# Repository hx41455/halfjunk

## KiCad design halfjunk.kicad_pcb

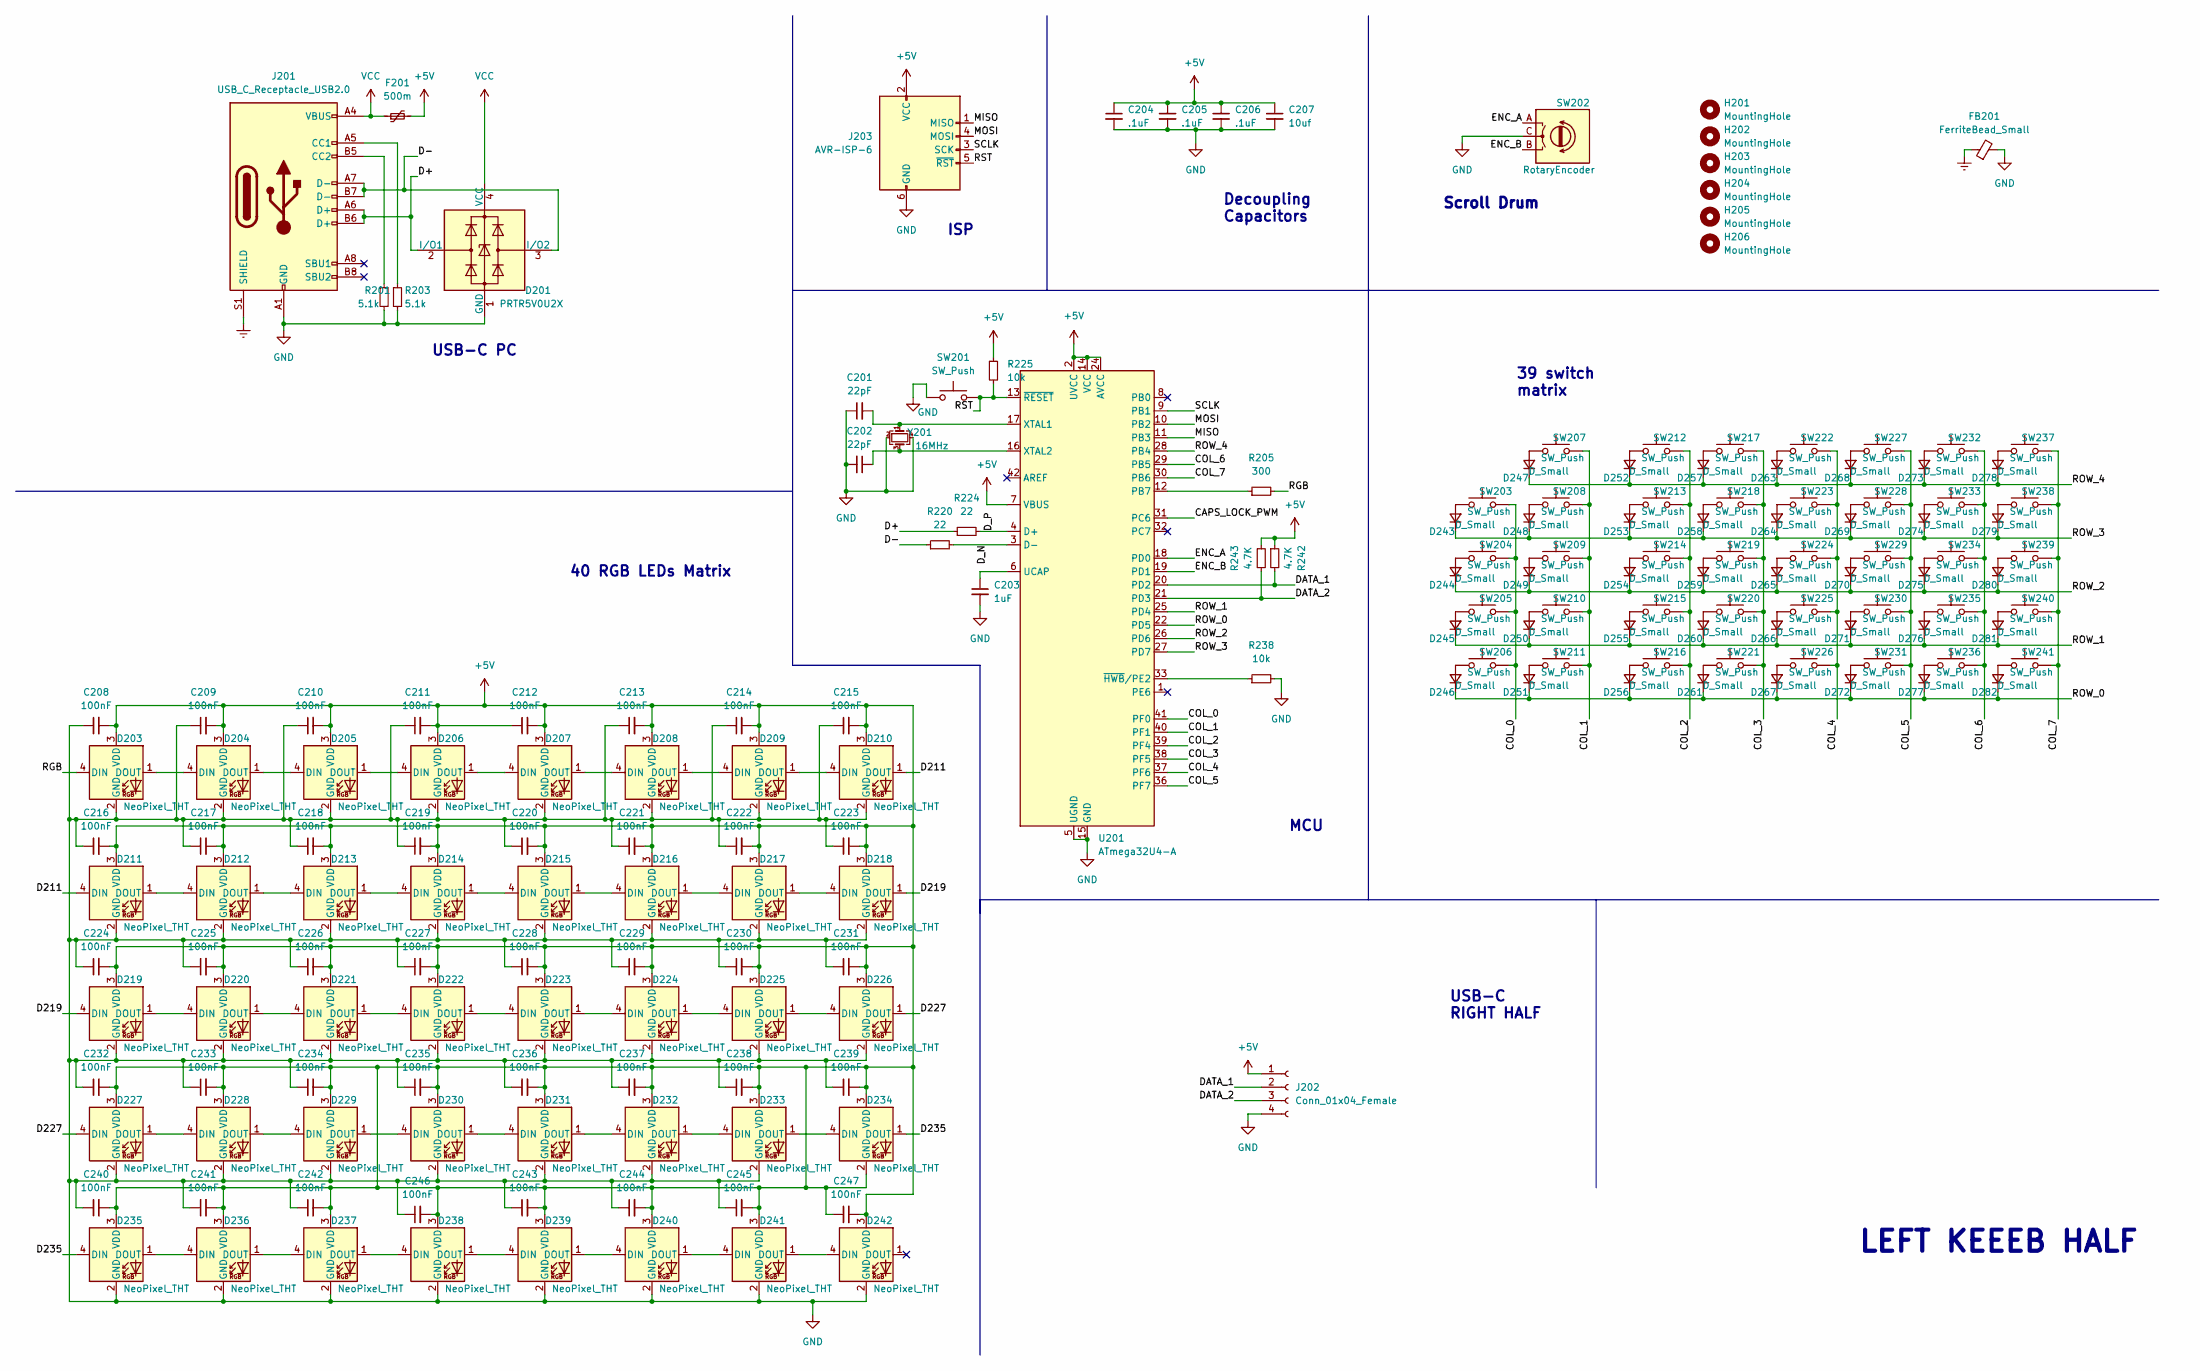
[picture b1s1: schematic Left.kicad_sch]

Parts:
C201, C202: 22pF; C_0402_1005Metric
C203: 1uF; C_0402_1005Metric
C204, C205, C206: .1uF; C_0402_1005Metric
C207: 10uf; C_0402_1005Metric
C208, C209, C210, C211, C212, C213, C214, C215, C216, C217, C218, C219, C220, C221, C222, C223, C224, C225, C226, C227, C228, C229, C230, C231, C232, C233, C234, C235, C236, C237, C238, C239, C240, C241, C242, C243, C244, C245, C246, C247: 100nF; C_0402_1005Metric
D201: PRTR5V0U2X; SOT-143
D203, D204, D205, D206, D207, D208, D209, D210, D211, D212, D213, D214, D215, D216, D217, D218, D219, D220, D221, D222, D223, D224, D225, D226, D227, D228, D229, D230, D231, D232, D233, D234, D235, D236, D237, D238, D239, D240, D241, D242: NeoPixel_THT; LED_RGB_Wuerth-PLCC4_3.2x2.8mm_150141M173100
D243, D244, D245, D246, D247, D248, D249, D250, D251, D252, D253, D254, D255, D256, D257, D258, D259, D260, D261, D263, D264, D265, D266, D267, D268, D269, D270, D271, D272, D273, D274, D275, D276, D277, D278, D279, D280, D281, D282: D_Small; D_SOD-123
F201: 500m; Fuse_0805
FB201: FerriteBead_Small; L_0805_2012Metric_Pad1.15x1.40mm_HandSolder
H201, H202, H203, H204, H205, H206: MountingHole; MountingHole_2.2mm_M2_DIN965_Pad
J201: USB_C_Receptacle_USB2.0; HRO-TYPE-C-31-M-13
J202: Conn_01x04_Female; I2C_Breakout
J203: AVR-ISP-6; ICSP-Header
R201, R203: 5.1k; R_0402_1005Metric
R205: 300; R_0402_1005Metric
R220, R224: 22; R_0402_1005Metric
R225, R238: 10k; R_0402_1005Metric
R242, R243: 4.7K; R_0402_1005Metric
SW201: SW_Push; SW_SPST_TL3342
SW202: RotaryEncoder; kailh_EN97xx_rotary_encoder
SW203, SW204, SW205, SW206, SW207, SW208, SW209, SW210, SW211, SW212, SW217, SW218, SW219, SW220, SW222, SW223, SW224, SW225, SW227, SW228, SW229, SW230, SW232, SW233, SW234, SW235, SW237, SW238, SW239, SW240, SW241: SW_Push; Kailh_socket_PG1350
SW213: SW_Push; Kailh_socket_PG1350_1.5U
SW214: SW_Push; Kailh_socket_PG1350_1.75U
SW215, SW236: SW_Push; Kailh_socket_PG1350_2.25U
SW216, SW221, SW226, SW231: SW_Push; Kailh_socket_PG1350_1.25U
U201: ATmega32U4-A; ATmega32U4
Y201: 16MHz; Crystal_SMD_3225-4Pin_3.2x2.5mm

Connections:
+5V: C204.1, C205.1, C206.1, C207.1, C208.2, C209.2, C210.2, C211.2, C212.1, C212.2, C213.2, C214.2, C215.2, C216.2, C217.2, C218.2, C219.2, C220.2, C221.2, C222.2, C223.2, C224.2, C225.2, C226.2, C227.2, C228.2, C229.2, C230.2, C231.2, C232.2, C233.2, C234.2, C235.2, C236.2, C237.2, C238.2, C239.2, C240.2, C241.2, C242.2, C243.2, C244.2, C245.2, C246.2, C247.1, C247.2, D203.3 (VDD), D204.3 (VDD), D205.3 (VDD), D206.3 (VDD), D207.3 (VDD), D208.3 (VDD), D209.3 (VDD), D210.3 (VDD), D211.3 (VDD), D212.3 (VDD), D213.3 (VDD), D214.3 (VDD), D215.3 (VDD), D216.3 (VDD), D217.3 (VDD), D218.3 (VDD), D219.3 (VDD), D220.3 (VDD), D221.3 (VDD), D222.3 (VDD), D223.3 (VDD), D224.3 (VDD), D225.3 (VDD), D226.3 (VDD), D227.3 (VDD), D228.3 (VDD), D229.3 (VDD), D230.3 (VDD), D231.3 (VDD), D232.3 (VDD), D233.3 (VDD), D234.2 (GND), D234.3 (VDD), D235.3 (VDD), D236.3 (VDD), D237.3 (VDD), D238.3 (VDD), D239.3 (VDD), D240.3 (VDD), D241.3 (VDD), D242.3 (VDD), F201.2, J202.1, J203.2 (VCC), R225.1, R242.1, R243.1, U201.2 (UVCC), U201.7 (VBUS), U201.14 (VCC), U201.24 (AVCC), U201.34 (VCC), U201.44 (AVCC); also elsewhere on the board
/Left/CAPS_LOCK_PWM: U201.31 (PC6)
/Left/COL_0: SW203.2, SW204.2, SW205.2, SW206.2, U201.41 (PF0)
/Left/COL_1: SW207.2, SW208.2, SW209.2, SW210.2, SW211.2, U201.40 (PF1)
/Left/COL_2: SW212.2, SW213.2, SW214.2, SW215.2, SW216.2, U201.39 (PF4)
/Left/COL_3: SW217.2, SW218.2, SW219.2, SW220.2, SW221.2, U201.38 (PF5)
/Left/COL_4: SW222.2, SW223.2, SW224.2, SW225.2, SW226.2, U201.37 (PF6)
/Left/COL_5: SW227.2, SW228.2, SW229.2, SW230.2, SW231.2, U201.36 (PF7)
/Left/COL_6: SW232.2, SW233.2, SW234.2, SW235.2, SW236.2, U201.29 (PB5)
/Left/COL_7: SW237.2, SW238.2, SW239.2, SW240.2, SW241.2, U201.30 (PB6)
/Left/D211: D210.1 (DOUT), D211.4 (DIN)
/Left/D219: D218.1 (DOUT), D219.4 (DIN)
/Left/D227: D226.1 (DOUT), D227.4 (DIN)
/Left/D235: D234.1 (DOUT), D235.4 (DIN)
/Left/D+: D201.2 (I/O1), J201.A6 (D+), J201.B6 (D+), R224.1
/Left/D-: D201.3 (I/O2), J201.A7 (D-), J201.B7 (D-), R220.1
/Left/DATA_1: J202.2, R242.2, U201.20 (PD2)
/Left/DATA_2: J202.3, R243.2, U201.21 (PD3)
/Left/D_N: R220.2, U201.3 (D-)
/Left/D_P: R224.2, U201.4 (D+)
/Left/ENC_A: SW202.A, U201.18 (PD0)
/Left/ENC_B: SW202.B, U201.19 (PD1)
/Left/MISO: J203.1 (MISO), U201.11 (PB3)
/Left/MOSI: J203.4 (MOSI), U201.10 (PB2)
/Left/RGB: D203.4 (DIN), R205.2
/Left/ROW_0: D246.1 (K), D251.1 (K), D256.1 (K), D261.1 (K), D267.1 (K), D272.1 (K), D277.1 (K), D282.1 (K), U201.22 (PD5)
/Left/ROW_1: D245.1 (K), D250.1 (K), D255.1 (K), D260.1 (K), D266.1 (K), D271.1 (K), D276.1 (K), D281.1 (K), U201.25 (PD4)
/Left/ROW_2: D244.1 (K), D249.1 (K), D254.1 (K), D259.1 (K), D265.1 (K), D270.1 (K), D275.1 (K), D280.1 (K), U201.26 (PD6)
/Left/ROW_3: D243.1 (K), D248.1 (K), D253.1 (K), D258.1 (K), D264.1 (K), D269.1 (K), D274.1 (K), D279.1 (K), U201.27 (PD7)
/Left/ROW_4: D247.1 (K), D252.1 (K), D257.1 (K), D263.1 (K), D268.1 (K), D273.1 (K), D278.1 (K), U201.28 (PB4)
/Left/RST: J203.5 (~RST), R225.2, SW201.2, U201.13 (~RESET)
/Left/SCLK: J203.3 (SCK), U201.9 (PB1)
Earth: FB201.1, J201.S1 (SHIELD); also elsewhere on the board
GND: C201.1, C202.2, C203.2, C204.2, C205.2, C206.2, C207.2, C208.1, C209.1, C210.1, C211.1, C213.1, C214.1, C215.1, C216.1, C217.1, C218.1, C219.1, C220.1, C221.1, C222.1, C223.1, C224.1, C225.1, C226.1, C227.1, C228.1, C229.1, C230.1, C231.1, C232.1, C233.1, C234.1, C235.1, C236.1, C237.1, C238.1, C239.1, C240.1, C241.1, C242.1, C243.1, C244.1, C245.1, C246.1, D201.1 (GND), D203.2 (GND), D204.2 (GND), D205.2 (GND), D206.2 (GND), D207.2 (GND), D208.2 (GND), D209.2 (GND), D210.2 (GND), D211.2 (GND), D212.2 (GND), D213.2 (GND), D214.2 (GND), D215.2 (GND), D216.2 (GND), D217.2 (GND), D218.2 (GND), D219.2 (GND), D220.2 (GND), D221.2 (GND), D222.2 (GND), D223.2 (GND), D224.2 (GND), D225.2 (GND), D226.2 (GND), D227.2 (GND), D228.2 (GND), D229.2 (GND), D230.2 (GND), D231.2 (GND), D232.2 (GND), D233.2 (GND), D235.2 (GND), D236.2 (GND), D237.2 (GND), D238.2 (GND), D239.2 (GND), D240.2 (GND), D241.2 (GND), D242.2 (GND), FB201.2, J201.A1 (GND), J201.A12 (GND), J201.B1 (GND), J201.B12 (GND), J202.4, J203.6 (GND), R201.2, R203.2, R238.2, SW201.1, SW202.C, U201.5 (UGND), U201.15 (GND), U201.23 (GND), U201.35 (GND), U201.43 (GND), Y201.2, Y201.4; also elsewhere on the board
unnamed: C201.2, U201.17 (XTAL1), Y201.1
unnamed: C202.1, U201.16 (XTAL2), Y201.3
unnamed: C203.1, U201.6 (UCAP)
unnamed: D203.1 (DOUT), D204.4 (DIN)
unnamed: D204.1 (DOUT), D205.4 (DIN)
unnamed: D205.1 (DOUT), D206.4 (DIN)
unnamed: D206.1 (DOUT), D207.4 (DIN)
unnamed: D207.1 (DOUT), D208.4 (DIN)
unnamed: D208.1 (DOUT), D209.4 (DIN)
unnamed: D209.1 (DOUT), D210.4 (DIN)
unnamed: D211.1 (DOUT), D212.4 (DIN)
unnamed: D212.1 (DOUT), D213.4 (DIN)
unnamed: D213.1 (DOUT), D214.4 (DIN)
unnamed: D214.1 (DOUT), D215.4 (DIN)
unnamed: D215.1 (DOUT), D216.4 (DIN)
unnamed: D216.1 (DOUT), D217.4 (DIN)
unnamed: D217.1 (DOUT), D218.4 (DIN)
unnamed: D219.1 (DOUT), D220.4 (DIN)
unnamed: D220.1 (DOUT), D221.4 (DIN)
unnamed: D221.1 (DOUT), D222.4 (DIN)
unnamed: D222.1 (DOUT), D223.4 (DIN)
unnamed: D223.1 (DOUT), D224.4 (DIN)
unnamed: D224.1 (DOUT), D225.4 (DIN)
unnamed: D225.1 (DOUT), D226.4 (DIN)
unnamed: D227.1 (DOUT), D228.4 (DIN)
unnamed: D228.1 (DOUT), D229.4 (DIN)
unnamed: D229.1 (DOUT), D230.4 (DIN)
unnamed: D230.1 (DOUT), D231.4 (DIN)
unnamed: D231.1 (DOUT), D232.4 (DIN)
unnamed: D232.1 (DOUT), D233.4 (DIN)
unnamed: D233.1 (DOUT), D234.4 (DIN)
unnamed: D235.1 (DOUT), D236.4 (DIN)
unnamed: D236.1 (DOUT), D237.4 (DIN)
unnamed: D237.1 (DOUT), D238.4 (DIN)
unnamed: D238.1 (DOUT), D239.4 (DIN)
unnamed: D239.1 (DOUT), D240.4 (DIN)
unnamed: D240.1 (DOUT), D241.4 (DIN)
unnamed: D241.1 (DOUT), D242.4 (DIN)
unnamed: D243.2 (A), SW203.1
unnamed: D244.2 (A), SW204.1
unnamed: D245.2 (A), SW205.1
unnamed: D246.2 (A), SW206.1
unnamed: D247.2 (A), SW207.1
unnamed: D248.2 (A), SW208.1
unnamed: D249.2 (A), SW209.1
unnamed: D250.2 (A), SW210.1
unnamed: D251.2 (A), SW211.1
unnamed: D252.2 (A), SW212.1
unnamed: D253.2 (A), SW213.1
unnamed: D254.2 (A), SW214.1
unnamed: D255.2 (A), SW215.1
unnamed: D256.2 (A), SW216.1
unnamed: D257.2 (A), SW217.1
unnamed: D258.2 (A), SW218.1
unnamed: D259.2 (A), SW219.1
unnamed: D260.2 (A), SW220.1
unnamed: D261.2 (A), SW221.1
unnamed: D263.2 (A), SW222.1
unnamed: D264.2 (A), SW223.1
unnamed: D265.2 (A), SW224.1
unnamed: D266.2 (A), SW225.1
unnamed: D267.2 (A), SW226.1
unnamed: D268.2 (A), SW227.1
unnamed: D269.2 (A), SW228.1
unnamed: D270.2 (A), SW229.1
unnamed: D271.2 (A), SW230.1
unnamed: D272.2 (A), SW231.1
unnamed: D273.2 (A), SW232.1
unnamed: D274.2 (A), SW233.1
unnamed: D275.2 (A), SW234.1
unnamed: D276.2 (A), SW235.1
unnamed: D277.2 (A), SW236.1
unnamed: D278.2 (A), SW237.1
unnamed: D279.2 (A), SW238.1
unnamed: D280.2 (A), SW239.1
unnamed: D281.2 (A), SW240.1
unnamed: D282.2 (A), SW241.1
unnamed: J201.A5 (CC1), R203.1
unnamed: J201.B5 (CC2), R201.1
unnamed: R205.1, U201.12 (PB7)
unnamed: R238.1, U201.33 (~HWB/PE2)
VCC: D201.4 (VCC), F201.1, J201.A4 (VBUS), J201.A9 (VBUS), J201.B4 (VBUS), J201.B9 (VBUS); also elsewhere on the board

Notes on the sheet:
39 switch matrix
USB-C RIGHT HALF
ISP
USB-C PC
40 RGB LEDs Matrix
Decoupling Capacitors
MCU
LEFT KEEEB HALF
Scroll Drum

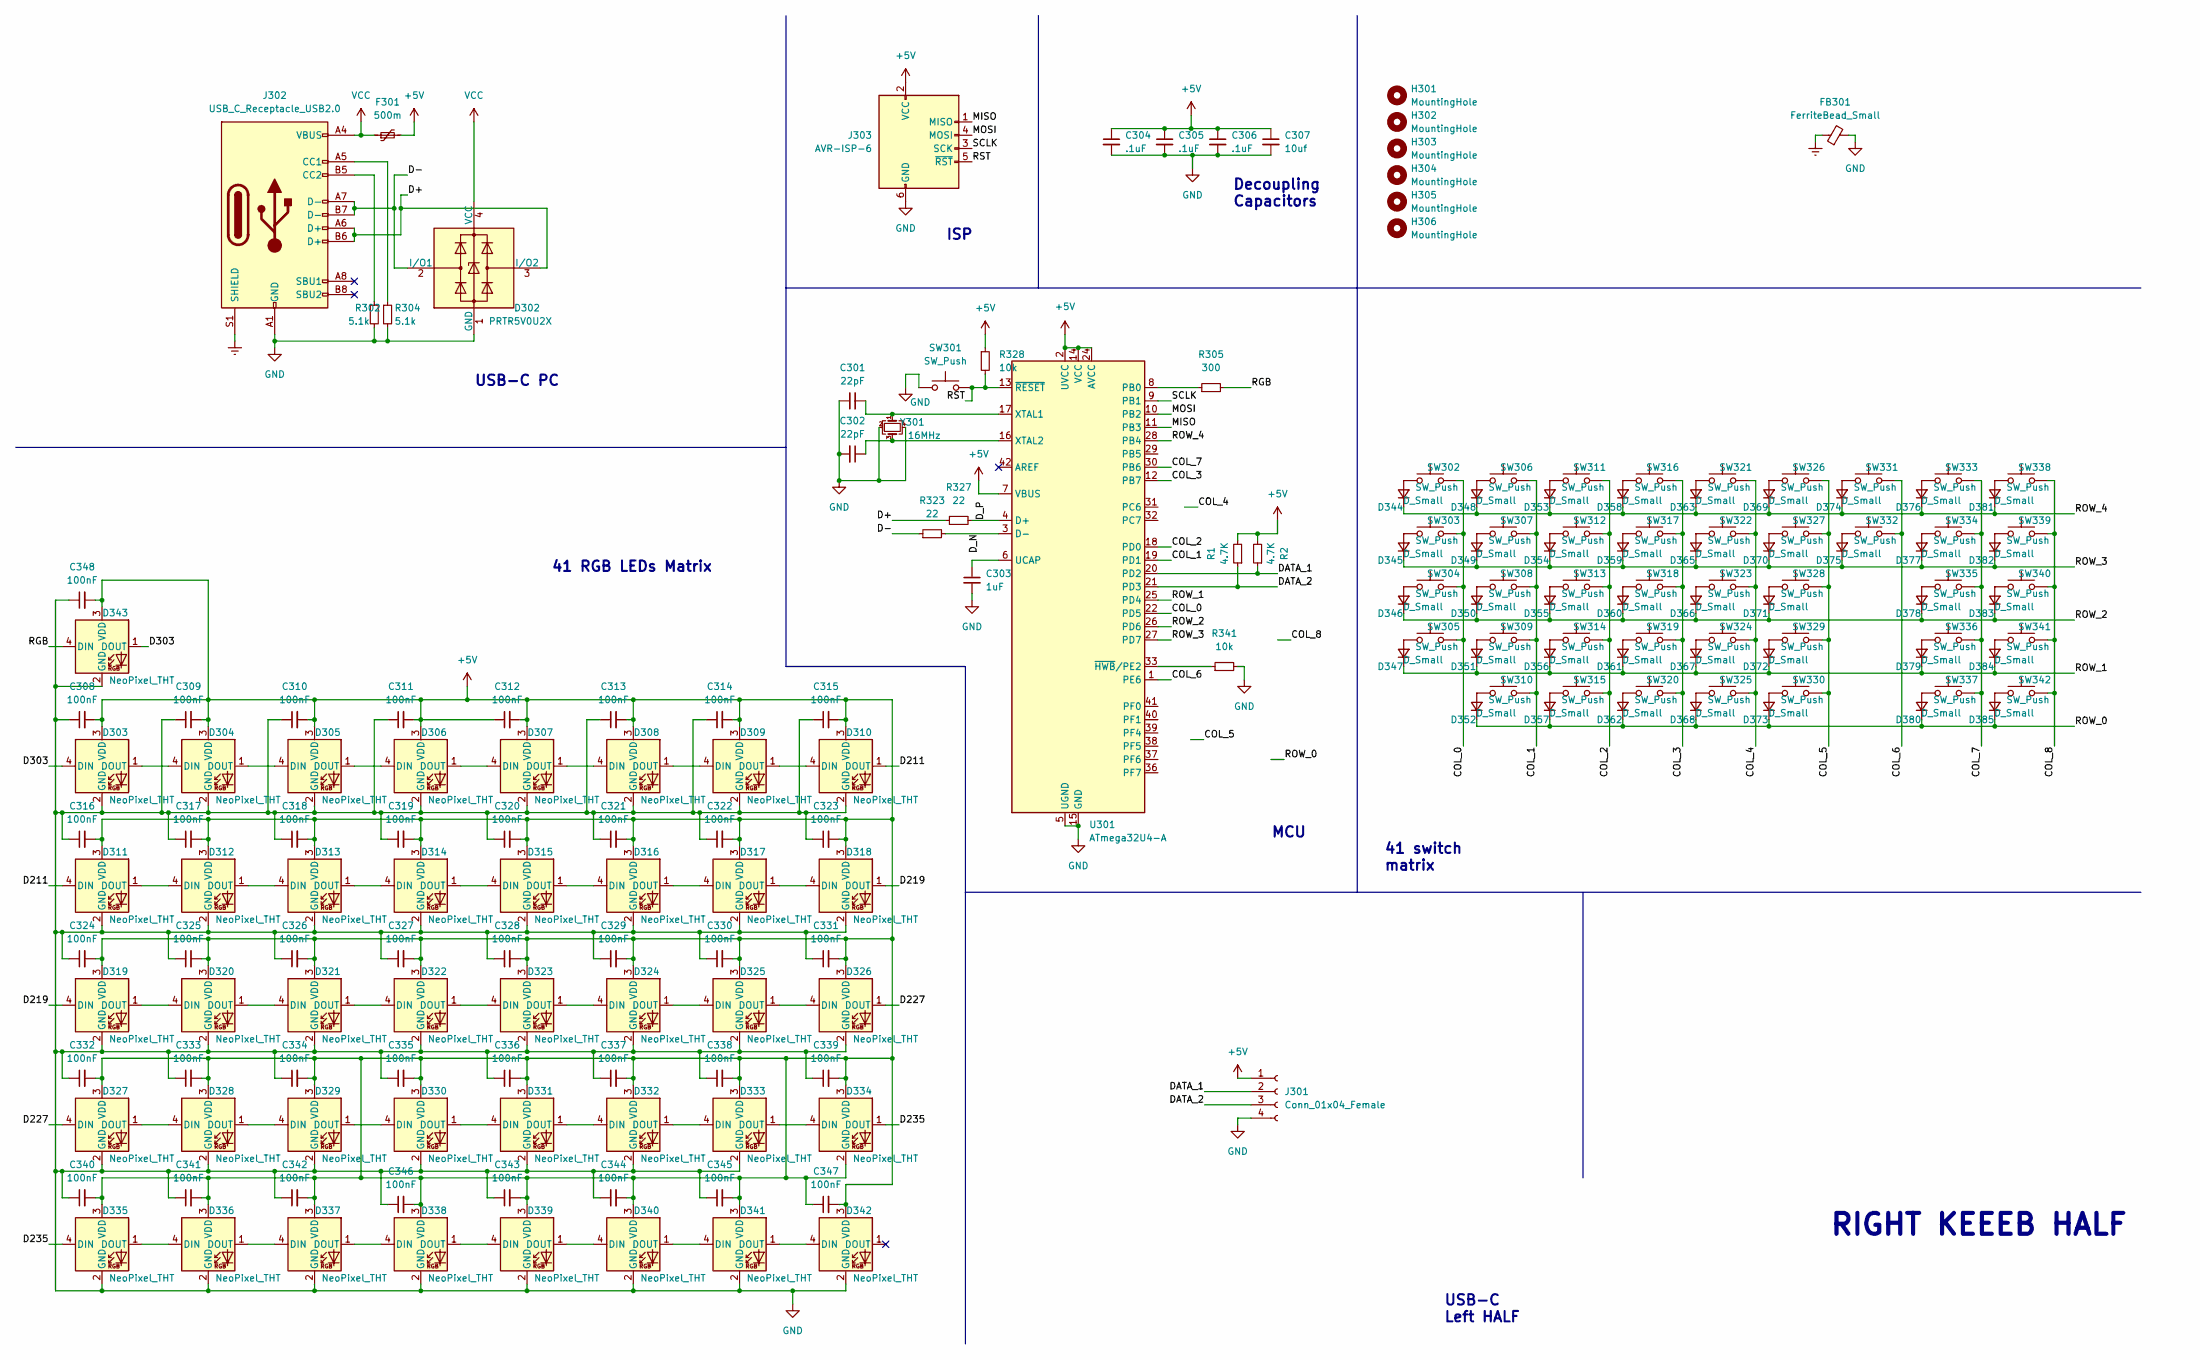
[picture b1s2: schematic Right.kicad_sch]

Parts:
C301, C302: 22pF; C_0402_1005Metric
C303: 1uF; C_0402_1005Metric
C304, C305, C306: .1uF; C_0402_1005Metric
C307: 10uf; C_0402_1005Metric
C308, C309, C310, C311, C312, C313, C314, C315, C316, C317, C318, C319, C320, C321, C322, C323, C324, C325, C326, C327, C328, C329, C330, C331, C332, C333, C334, C335, C336, C337, C338, C339, C340, C341, C342, C343, C344, C345, C346, C347, C348: 100nF; C_0402_1005Metric
D302: PRTR5V0U2X; SOT-143
D303, D304, D305, D306, D307, D308, D309, D310, D311, D312, D313, D314, D315, D316, D317, D318, D319, D320, D321, D322, D323, D324, D325, D326, D327, D328, D329, D330, D331, D332, D333, D334, D335, D336, D337, D338, D339, D340, D341, D342, D343: NeoPixel_THT; LED_RGB_Wuerth-PLCC4_3.2x2.8mm_150141M173100
D344, D345, D346, D347, D348, D349, D350, D351, D352, D353, D354, D355, D356, D357, D358, D359, D360, D361, D362, D363, D365, D366, D367, D368, D369, D370, D371, D372, D373, D374, D375, D376, D377, D378, D379, D380, D381, D382, D383, D384, D385: D_Small; D_SOD-123
F301: 500m; Fuse_0805
FB301: FerriteBead_Small; L_0805_2012Metric_Pad1.15x1.40mm_HandSolder
H301, H302, H303, H304, H305, H306: MountingHole; MountingHole_2.2mm_M2_DIN965_Pad
J301: Conn_01x04_Female; I2C_Breakout
J302: USB_C_Receptacle_USB2.0; HRO-TYPE-C-31-M-13
J303: AVR-ISP-6; ICSP-Header
R1, R2: 4.7K; R_0402_1005Metric
R302, R304: 5.1k; R_0402_1005Metric
R305: 300; R_0402_1005Metric
R323, R327: 22; R_0402_1005Metric
R328, R341: 10k; R_0402_1005Metric
SW301: SW_Push; SW_SPST_TL3342
SW302, SW303, SW304, SW305, SW306, SW307, SW308, SW309, SW311, SW312, SW313, SW314, SW316, SW317, SW318, SW319, SW320, SW321, SW322, SW323, SW324, SW325, SW326, SW327, SW328, SW330, SW331, SW332, SW333, SW336, SW337, SW338, SW339, SW340, SW341, SW342: SW_Push; Kailh_socket_PG1350
SW310, SW335: SW_Push; Kailh_socket_PG1350_2.25U
SW315: SW_Push; Kailh_socket_PG1350_1.25U
SW329: SW_Push; Kailh_socket_PG1350_1.75U
SW334: SW_Push; Kailh_socket_PG1350_1.5U
U301: ATmega32U4-A; ATmega32U4
Y301: 16MHz; Crystal_SMD_3225-4Pin_3.2x2.5mm

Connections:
+5V: C304.1, C305.1, C306.1, C307.1, C308.2, C309.2, C310.2, C311.2, C312.1, C312.2, C313.2, C314.2, C315.2, C316.2, C317.2, C318.2, C319.2, C320.2, C321.2, C322.2, C323.2, C324.2, C325.2, C326.2, C327.2, C328.2, C329.2, C330.2, C331.2, C332.2, C333.2, C334.2, C335.2, C336.2, C337.2, C338.2, C339.2, C340.2, C341.2, C342.2, C343.2, C344.2, C345.2, C346.2, C347.1, C347.2, C348.2, D303.3 (VDD), D304.3 (VDD), D305.3 (VDD), D306.3 (VDD), D307.3 (VDD), D308.3 (VDD), D309.3 (VDD), D310.3 (VDD), D311.3 (VDD), D312.3 (VDD), D313.3 (VDD), D314.3 (VDD), D315.3 (VDD), D316.3 (VDD), D317.3 (VDD), D318.3 (VDD), D319.3 (VDD), D320.3 (VDD), D321.3 (VDD), D322.3 (VDD), D323.3 (VDD), D324.3 (VDD), D325.3 (VDD), D326.3 (VDD), D327.3 (VDD), D328.3 (VDD), D329.3 (VDD), D330.3 (VDD), D331.3 (VDD), D332.3 (VDD), D333.3 (VDD), D334.2 (GND), D334.3 (VDD), D335.3 (VDD), D336.3 (VDD), D337.3 (VDD), D338.3 (VDD), D339.3 (VDD), D340.3 (VDD), D341.3 (VDD), D342.3 (VDD), D343.3 (VDD), F301.2, J301.1, J303.2 (VCC), R1.2, R2.2, R328.1, U301.2 (UVCC), U301.7 (VBUS), U301.14 (VCC), U301.24 (AVCC), U301.34 (VCC), U301.44 (AVCC); also elsewhere on the board
/Right/COL_0: SW302.2, SW303.2, SW304.2, SW305.2, U301.22 (PD5)
/Right/COL_1: SW306.2, SW307.2, SW308.2, SW309.2, SW310.2, U301.19 (PD1)
/Right/COL_2: SW311.2, SW312.2, SW313.2, SW314.2, SW315.2, U301.18 (PD0)
/Right/COL_3: SW316.2, SW317.2, SW318.2, SW319.2, SW320.2, U301.12 (PB7)
/Right/COL_4: SW321.2, SW322.2, SW323.2, SW324.2, SW325.2
/Right/COL_5: SW326.2, SW327.2, SW328.2, SW329.2, SW330.2
/Right/COL_6: SW331.2, SW332.2, U301.1 (PE6)
/Right/COL_7: SW333.2, SW334.2, SW335.2, SW336.2, SW337.2, U301.30 (PB6)
/Right/COL_8: SW338.2, SW339.2, SW340.2, SW341.2, SW342.2
/Right/D211: D310.1 (DOUT), D311.4 (DIN)
/Right/D219: D318.1 (DOUT), D319.4 (DIN)
/Right/D227: D326.1 (DOUT), D327.4 (DIN)
/Right/D235: D334.1 (DOUT), D335.4 (DIN)
/Right/D303: D303.4 (DIN), D343.1 (DOUT)
/Right/D+: D302.3 (I/O2), J302.A6 (D+), J302.B6 (D+), R327.1
/Right/D-: D302.2 (I/O1), J302.A7 (D-), J302.B7 (D-), R323.1
/Right/DATA_1: J301.2, R2.1, U301.20 (PD2)
/Right/DATA_2: J301.3, R1.1, U301.21 (PD3)
/Right/D_N: R323.2, U301.3 (D-)
/Right/D_P: R327.2, U301.4 (D+)
/Right/MISO: J303.1 (MISO), U301.11 (PB3)
/Right/MOSI: J303.4 (MOSI), U301.10 (PB2)
/Right/RGB: D343.4 (DIN), R305.2
/Right/ROW_0: D352.1 (K), D357.1 (K), D362.1 (K), D368.1 (K), D373.1 (K), D380.1 (K), D385.1 (K)
/Right/ROW_1: D347.1 (K), D351.1 (K), D356.1 (K), D361.1 (K), D367.1 (K), D372.1 (K), D379.1 (K), D384.1 (K), U301.25 (PD4)
/Right/ROW_2: D346.1 (K), D350.1 (K), D355.1 (K), D360.1 (K), D366.1 (K), D371.1 (K), D378.1 (K), D383.1 (K), U301.26 (PD6)
/Right/ROW_3: D345.1 (K), D349.1 (K), D354.1 (K), D359.1 (K), D365.1 (K), D370.1 (K), D375.1 (K), D377.1 (K), D382.1 (K), U301.27 (PD7)
/Right/ROW_4: D344.1 (K), D348.1 (K), D353.1 (K), D358.1 (K), D363.1 (K), D369.1 (K), D374.1 (K), D376.1 (K), D381.1 (K), U301.28 (PB4)
/Right/RST: J303.5 (~RST), R328.2, SW301.2, U301.13 (~RESET)
/Right/SCLK: J303.3 (SCK), U301.9 (PB1)
Earth: FB301.1, J302.S1 (SHIELD); also elsewhere on the board
GND: C301.1, C302.2, C303.2, C304.2, C305.2, C306.2, C307.2, C308.1, C309.1, C310.1, C311.1, C313.1, C314.1, C315.1, C316.1, C317.1, C318.1, C319.1, C320.1, C321.1, C322.1, C323.1, C324.1, C325.1, C326.1, C327.1, C328.1, C329.1, C330.1, C331.1, C332.1, C333.1, C334.1, C335.1, C336.1, C337.1, C338.1, C339.1, C340.1, C341.1, C342.1, C343.1, C344.1, C345.1, C346.1, C348.1, D302.1 (GND), D303.2 (GND), D304.2 (GND), D305.2 (GND), D306.2 (GND), D307.2 (GND), D308.2 (GND), D309.2 (GND), D310.2 (GND), D311.2 (GND), D312.2 (GND), D313.2 (GND), D314.2 (GND), D315.2 (GND), D316.2 (GND), D317.2 (GND), D318.2 (GND), D319.2 (GND), D320.2 (GND), D321.2 (GND), D322.2 (GND), D323.2 (GND), D324.2 (GND), D325.2 (GND), D326.2 (GND), D327.2 (GND), D328.2 (GND), D329.2 (GND), D330.2 (GND), D331.2 (GND), D332.2 (GND), D333.2 (GND), D335.2 (GND), D336.2 (GND), D337.2 (GND), D338.2 (GND), D339.2 (GND), D340.2 (GND), D341.2 (GND), D342.2 (GND), D343.2 (GND), FB301.2, J301.4, J302.A1 (GND), J302.A12 (GND), J302.B1 (GND), J302.B12 (GND), J303.6 (GND), R302.2, R304.2, R341.2, SW301.1, U301.5 (UGND), U301.15 (GND), U301.23 (GND), U301.35 (GND), U301.43 (GND), Y301.2, Y301.4; also elsewhere on the board
unnamed: C301.2, U301.17 (XTAL1), Y301.1
unnamed: C302.1, U301.16 (XTAL2), Y301.3
unnamed: C303.1, U301.6 (UCAP)
unnamed: D303.1 (DOUT), D304.4 (DIN)
unnamed: D304.1 (DOUT), D305.4 (DIN)
unnamed: D305.1 (DOUT), D306.4 (DIN)
unnamed: D306.1 (DOUT), D307.4 (DIN)
unnamed: D307.1 (DOUT), D308.4 (DIN)
unnamed: D308.1 (DOUT), D309.4 (DIN)
unnamed: D309.1 (DOUT), D310.4 (DIN)
unnamed: D311.1 (DOUT), D312.4 (DIN)
unnamed: D312.1 (DOUT), D313.4 (DIN)
unnamed: D313.1 (DOUT), D314.4 (DIN)
unnamed: D314.1 (DOUT), D315.4 (DIN)
unnamed: D315.1 (DOUT), D316.4 (DIN)
unnamed: D316.1 (DOUT), D317.4 (DIN)
unnamed: D317.1 (DOUT), D318.4 (DIN)
unnamed: D319.1 (DOUT), D320.4 (DIN)
unnamed: D320.1 (DOUT), D321.4 (DIN)
unnamed: D321.1 (DOUT), D322.4 (DIN)
unnamed: D322.1 (DOUT), D323.4 (DIN)
unnamed: D323.1 (DOUT), D324.4 (DIN)
unnamed: D324.1 (DOUT), D325.4 (DIN)
unnamed: D325.1 (DOUT), D326.4 (DIN)
unnamed: D327.1 (DOUT), D328.4 (DIN)
unnamed: D328.1 (DOUT), D329.4 (DIN)
unnamed: D329.1 (DOUT), D330.4 (DIN)
unnamed: D330.1 (DOUT), D331.4 (DIN)
unnamed: D331.1 (DOUT), D332.4 (DIN)
unnamed: D332.1 (DOUT), D333.4 (DIN)
unnamed: D333.1 (DOUT), D334.4 (DIN)
unnamed: D335.1 (DOUT), D336.4 (DIN)
unnamed: D336.1 (DOUT), D337.4 (DIN)
unnamed: D337.1 (DOUT), D338.4 (DIN)
unnamed: D338.1 (DOUT), D339.4 (DIN)
unnamed: D339.1 (DOUT), D340.4 (DIN)
unnamed: D340.1 (DOUT), D341.4 (DIN)
unnamed: D341.1 (DOUT), D342.4 (DIN)
unnamed: D344.2 (A), SW302.1
unnamed: D345.2 (A), SW303.1
unnamed: D346.2 (A), SW304.1
unnamed: D347.2 (A), SW305.1
unnamed: D348.2 (A), SW306.1
unnamed: D349.2 (A), SW307.1
unnamed: D350.2 (A), SW308.1
unnamed: D351.2 (A), SW309.1
unnamed: D352.2 (A), SW310.1
unnamed: D353.2 (A), SW311.1
unnamed: D354.2 (A), SW312.1
unnamed: D355.2 (A), SW313.1
unnamed: D356.2 (A), SW314.1
unnamed: D357.2 (A), SW315.1
unnamed: D358.2 (A), SW316.1
unnamed: D359.2 (A), SW317.1
unnamed: D360.2 (A), SW318.1
unnamed: D361.2 (A), SW319.1
unnamed: D362.2 (A), SW320.1
unnamed: D363.2 (A), SW321.1
unnamed: D365.2 (A), SW322.1
unnamed: D366.2 (A), SW323.1
unnamed: D367.2 (A), SW324.1
unnamed: D368.2 (A), SW325.1
unnamed: D369.2 (A), SW326.1
unnamed: D370.2 (A), SW327.1
unnamed: D371.2 (A), SW328.1
unnamed: D372.2 (A), SW329.1
unnamed: D373.2 (A), SW330.1
unnamed: D374.2 (A), SW331.1
unnamed: D375.2 (A), SW332.1
unnamed: D376.2 (A), SW333.1
unnamed: D377.2 (A), SW334.1
unnamed: D378.2 (A), SW335.1
unnamed: D379.2 (A), SW336.1
unnamed: D380.2 (A), SW337.1
unnamed: D381.2 (A), SW338.1
unnamed: D382.2 (A), SW339.1
unnamed: D383.2 (A), SW340.1
unnamed: D384.2 (A), SW341.1
unnamed: D385.2 (A), SW342.1
unnamed: J302.A5 (CC1), R304.1
unnamed: J302.B5 (CC2), R302.1
unnamed: R305.1, U301.8 (PB0)
unnamed: R341.1, U301.33 (~HWB/PE2)
VCC: D302.4 (VCC), F301.1, J302.A4 (VBUS), J302.A9 (VBUS), J302.B4 (VBUS), J302.B9 (VBUS); also elsewhere on the board

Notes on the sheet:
41 switch matrix
USB-C PC
USB-C Left HALF
MCU
Decoupling Capacitors
RIGHT KEEEB HALF
ISP
41 RGB LEDs Matrix

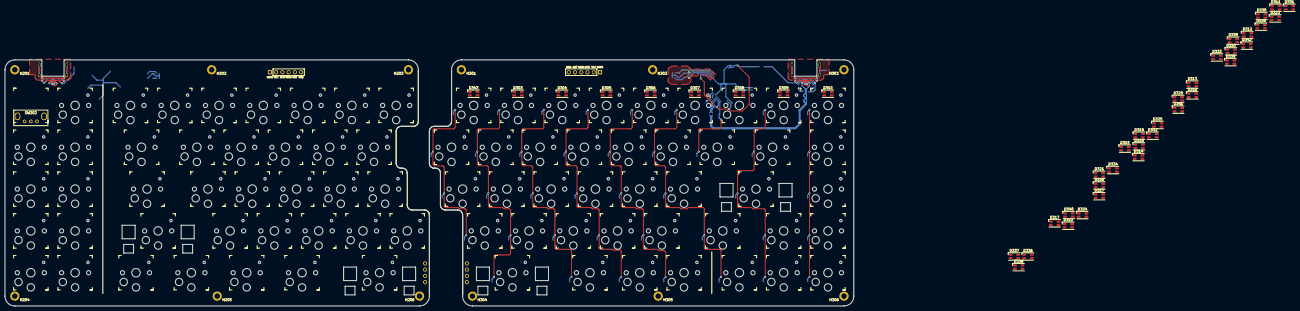
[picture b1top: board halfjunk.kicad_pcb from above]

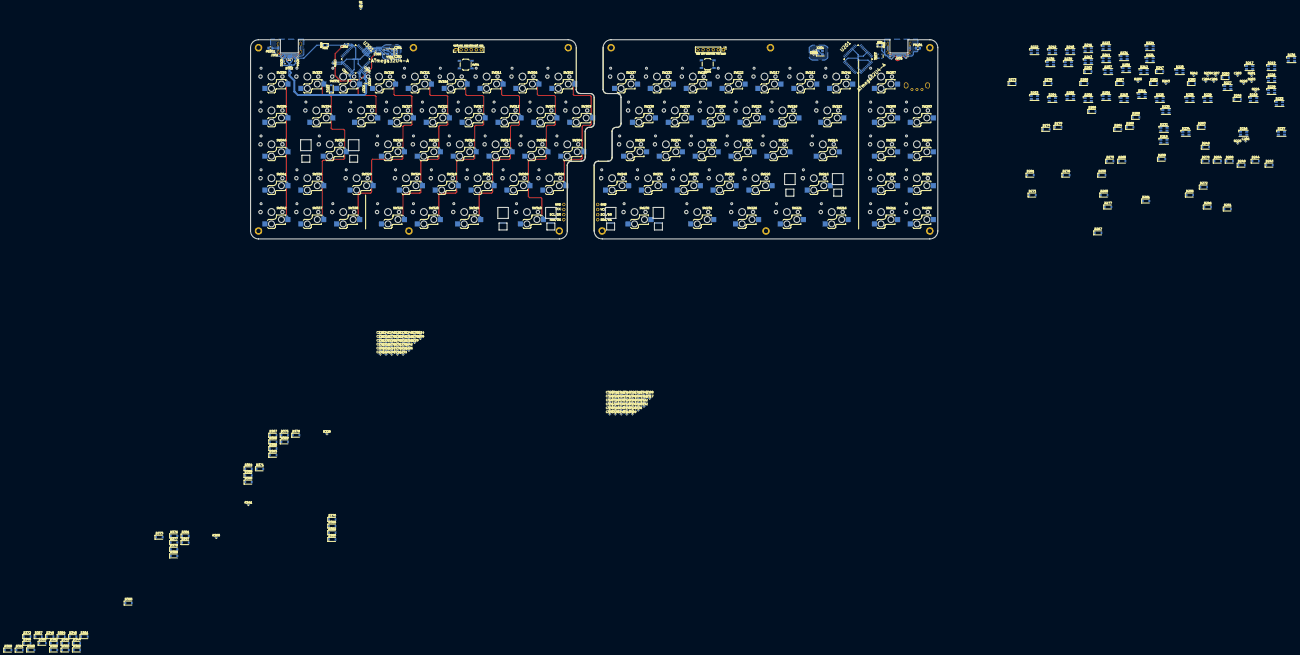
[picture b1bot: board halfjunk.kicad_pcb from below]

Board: 2 copper layers, 345.0 x 100.0 mm, 385 parts (251 on the bottom side), 228 nets.
